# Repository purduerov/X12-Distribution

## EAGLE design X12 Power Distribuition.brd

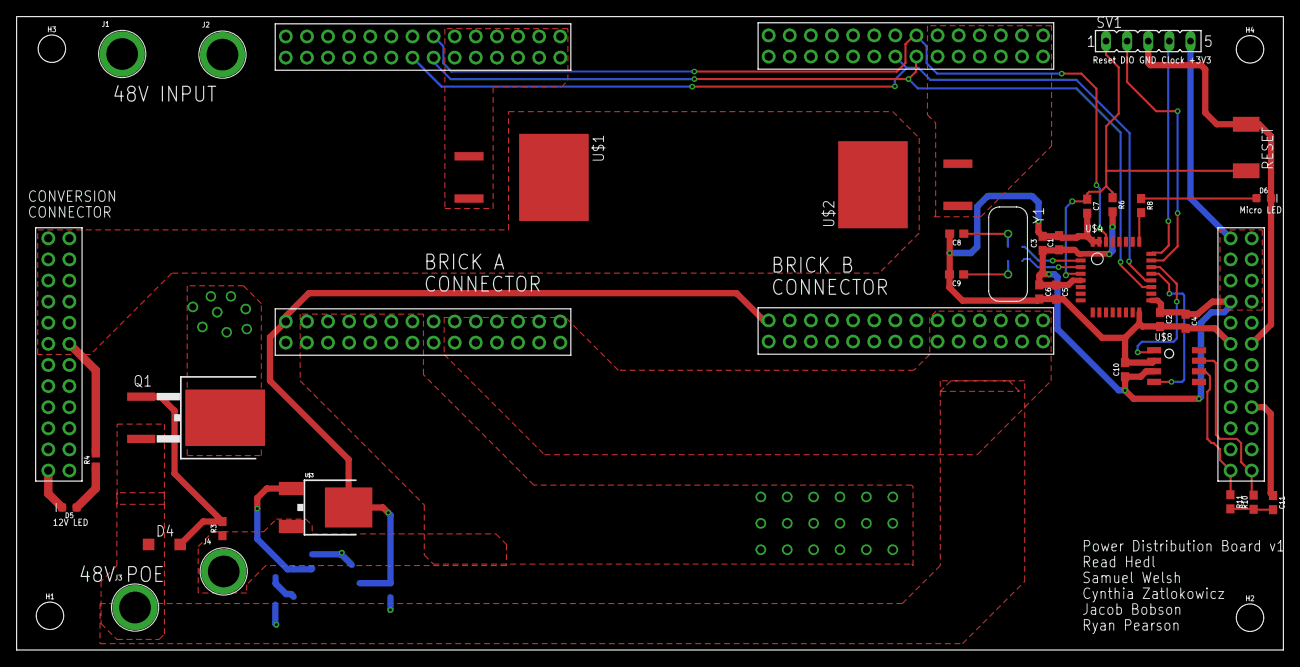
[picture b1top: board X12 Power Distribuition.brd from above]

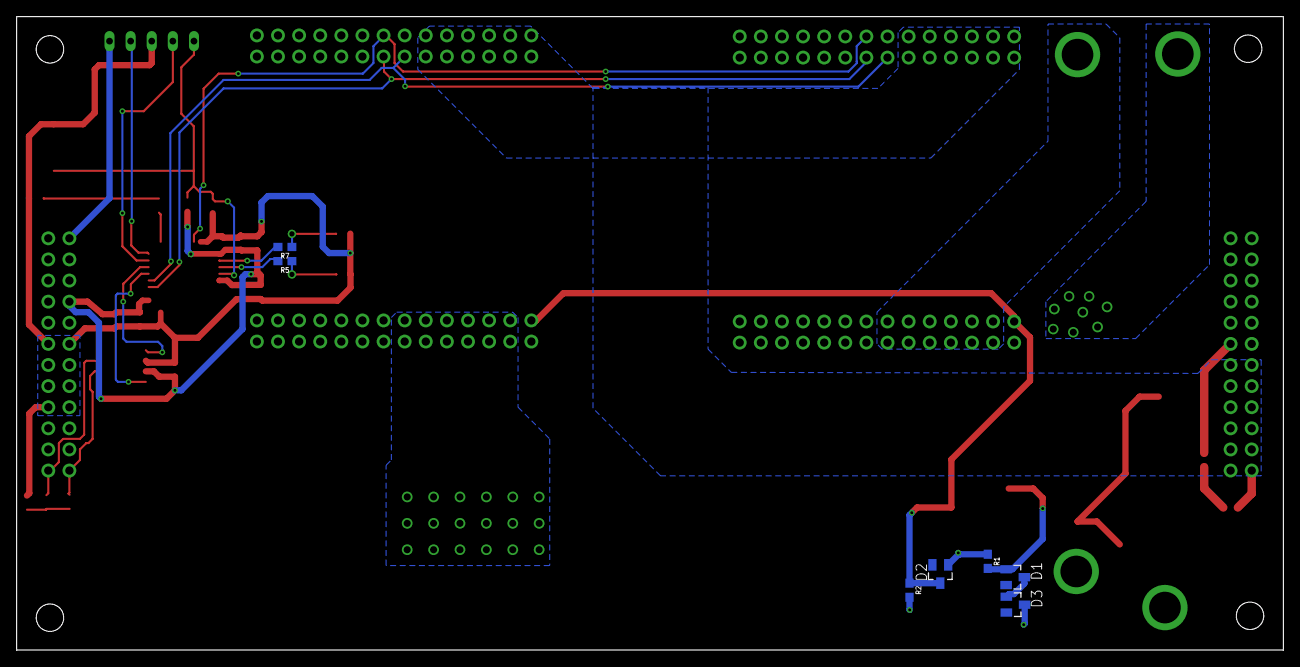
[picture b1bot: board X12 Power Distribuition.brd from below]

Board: 2 copper layers, 152.4 x 76.2 mm, 47 parts (7 on the bottom side), 31 nets.

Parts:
C1, C2, C3, C4, C5, C6, C7, C8, C9, C10: 4.7uF; 0603
C11: 0.1uF; 0603
D1, D3: 22V; SOT23
D2: 5V; SOT23
D4: 15V; SOD123
D5, D6: LED-0603
H1, H2, H3, H4: STAND-OFF
J1, J2, J3, J4: BANANA_CONN
Q1: SPB80P06P; TO263
R1, R3: 1M; 0603
R2: 10K; 0603
R4, R8: 470; 0603
R5, R6, R7: 1k; 0603
R10, R11: 60; 0603
RESET: SW_2512
SV1: FE05-1
U$1, U$2: DIODE
U$3: NMOSFET-DPAK; DPAK
U$4: STM32F042K6T6
U$5, U$7: BRICKBOARD_TSW_14X2
U$6: CONVERSION_TSW_12X2
U$8: TCAN337D
Y1: ECS-80-S-4X; XTAL_ECS-80-S-4X

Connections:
3V3GND: C1.2, C2.2, C3.2, C4.2, C5.2, C6.2, C7.2, C8.2, C9.2, C10.2, C11.1, D6.C, RESET.1, SV1.3, U$4.PB8-BOOT0, U$4.VSS, U$4.VSS1, U$6.35, U$6.36, U$6.37, U$6.38, U$6.39, U$6.40, U$6.41, U$6.42, U$8.GND
48V_GND: D2.1, J2.P$1, J4.P$1, R1.1, R3.1, U$3.3, U$5.3, U$5.4, U$5.5, U$5.6, U$5.7, U$5.8, U$5.9, U$5.10, U$5.11, U$5.12, U$5.13, U$5.14, U$7.3, U$7.4, U$7.5, U$7.6, U$7.7, U$7.8, U$7.9, U$7.10, U$7.11, U$7.12, U$7.13, U$7.14
+3V3: C1.1, C2.1, C3.1, C4.1, C5.1, C6.1, C10.1, R6.2, SV1.5, U$4.VDD, U$4.VDDA, U$4.VDDIO2, U$6.25, U$6.26, U$6.27, U$6.28, U$6.29, U$6.30, U$6.31, U$6.32, U$8.VCC
+12V: R4.2, U$1.OUT, U$2.OUT, U$6.1, U$6.2, U$6.3, U$6.4, U$6.5, U$6.6, U$6.7, U$6.8, U$6.9, U$6.10, U$6.11, U$6.12
+12V_A: U$1.IN1, U$1.IN2, U$7.45, U$7.46, U$7.47, U$7.48, U$7.49, U$7.50, U$7.51, U$7.52, U$7.53, U$7.54, U$7.55, U$7.56
+12V_B: U$2.IN1, U$2.IN2, U$5.45, U$5.46, U$5.47, U$5.48, U$5.49, U$5.50, U$5.51, U$5.52, U$5.53, U$5.54, U$5.55, U$5.56
+48V: D3.3, D4.C, J3.P$1, Q1.2, R2.2, U$5.17, U$5.18, U$5.19, U$5.20, U$5.21, U$5.22, U$5.23, U$5.24, U$5.25, U$5.26, U$5.27, U$5.28, U$7.17, U$7.18, U$7.19, U$7.20, U$7.21, U$7.22, U$7.23, U$7.24, U$7.25, U$7.26, U$7.27, U$7.28
+48V_RAW: J1.P$1, Q1.3
ALERT: U$4.PB7, U$5.43, U$7.43
CAN_H: R10.2, U$6.47, U$8.CANH
CAN_L: R11.1, U$6.48, U$8.CANL
CAN_RX: U$4.PA11, U$8.RXD
CAN_TX: U$4.PA12, U$8.TXD
CLK: U$4.PA9, U$5.44, U$7.44
DATA: U$4.PA10, U$5.42, U$7.42
GND: D5.C, U$5.29, U$5.30, U$5.31, U$5.32, U$5.33, U$5.34, U$5.35, U$5.36, U$5.37, U$5.38, U$5.39, U$5.40, U$6.13, U$6.14, U$6.15, U$6.16, U$6.17, U$6.18, U$6.19, U$6.20, U$6.21, U$6.22, U$6.23, U$6.24, U$7.29, U$7.30, U$7.31, U$7.32, U$7.33, U$7.34, U$7.35, U$7.36, U$7.37, U$7.38, U$7.39, U$7.40
LED: R8.2, U$4.PA15
unnamed: D1.3, D3.1
unnamed: D1.1, R1.2, U$3.1
unnamed: D4.A, Q1.1, R3.2
unnamed: D5.A, R4.1
unnamed: C11.2, R10.1, R11.2
unnamed: C9.1, R5.1, Y1.2
unnamed: C8.1, R7.1, Y1.1
unnamed: D6.A, R8.1
NRST: C7.1, R6.1, RESET.2, SV1.1, U$4.NRST
ON/OFF: D2.3, R2.1, U$3.4, U$5.1, U$7.1
OSC_IN: R7.2, U$4.PF0-OSC_IN
OSC_OUT: R5.2, U$4.PF1-OSC_OUT
SWCLK: SV1.4, U$4.PA14
SWDIO: SV1.2, U$4.PA13

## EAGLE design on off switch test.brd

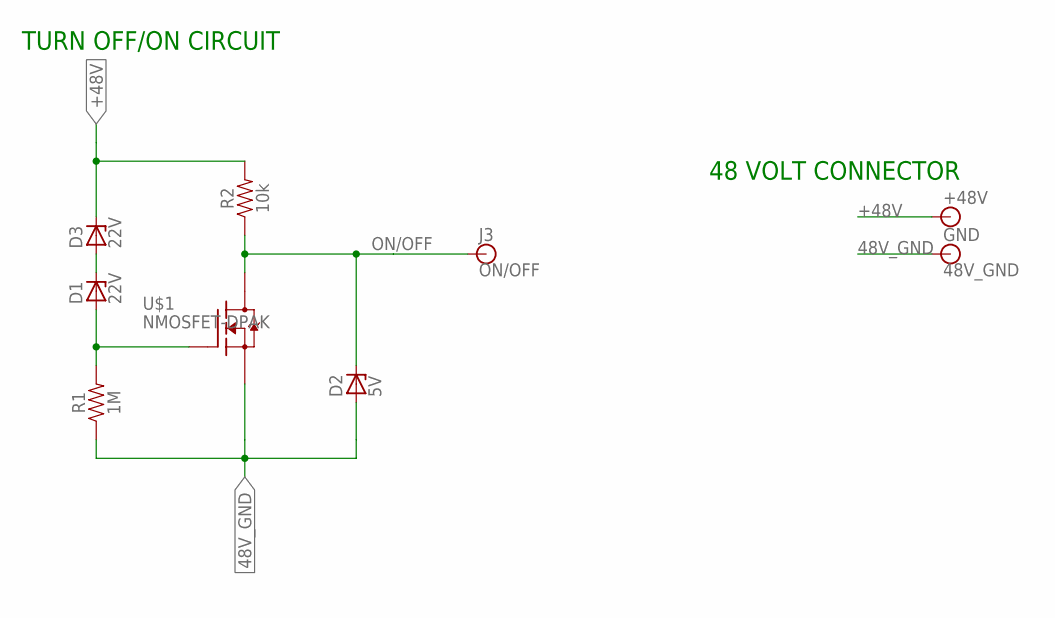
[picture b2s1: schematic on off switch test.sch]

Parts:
+48V: BANANA_CONN
D1, D3: 22V; SOT23
D2: 5V; SOT23
GND: 48V_GND; BANANA_CONN
J3: ON/OFF; BANANA_CONN
R1: 1M; 0603
R2: 10k; 0603
U$1: NMOSFET-DPAK; DPAK

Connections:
48V_GND: D2.1 (A), GND.P$1, R1.1, U$1.3 (S)
+48V: +48V.P$1, D3.3 (C), R2.2
unnamed: D1.3 (C), D3.1 (A)
unnamed: D1.1 (A), R1.2, U$1.1 (G)
ON/OFF: D2.3 (C), J3.P$1, R2.1, U$1.4 (D1)

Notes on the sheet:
48 VOLT CONNECTOR
TURN OFF/ON CIRCUIT

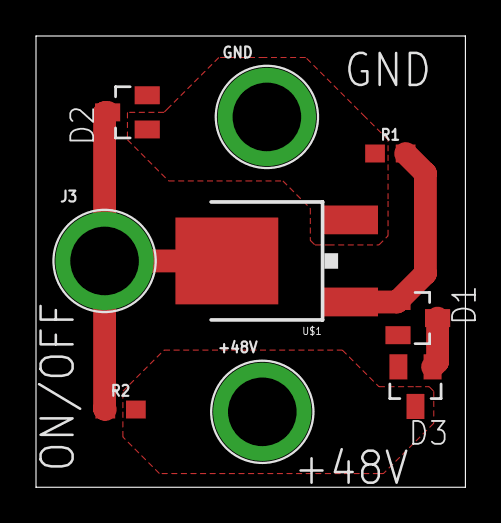
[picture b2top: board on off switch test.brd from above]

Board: 2 copper layers, 23.9 x 25.1 mm, 9 parts (0 on the bottom side), 5 nets.

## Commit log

2019-09-25 created schematic
    (:
2019-09-25 Prelim power distribution schematic
2019-09-25 Test Commit
    Nothing Changed ;)
2019-09-25 Cleaning
2019-10-09 Added Micro
2019-10-12 Micro Added
2019-10-14 Added POE through holes
2019-10-19 Label Fix
2019-10-19 Resistor Values
2019-10-19 clean
2019-10-19 Started Brick Connector
2019-10-22 Prototype Conversion Connector
2019-10-23 test
2019-10-23 Created connectors
2019-10-24 Completed prelim schematic
2019-10-24 created initial connector layout on board
2019-10-29 altered board
2019-10-30 worked on board
2019-11-02 Started Board Placement
2019-11-03 updated connector
2019-11-03 added standoffs
    added the standoffs to the board
2019-11-06 Board
2019-11-06 removed junk pt 1
2019-11-07 modified micro section
2019-11-07 Update X12 Power Distribuition 2.b#1
2019-11-07 Fixed Brickboard Connectors
2019-11-09 finished up prelim board
2019-11-10 fixed some erc warnings
2019-11-10 modified cap placements
2019-11-10 Update X12 Power Distribuition.b##
2019-11-10 more modifications
2019-11-11 Small edits on board
    Added Labels
2019-11-14 Board Fixes around Micro
2019-11-14 Matched Impedances around crystal
2019-11-16 Moved Crystal. Small Fixes
2019-11-16 adjusted thermals
2019-11-16 micro pin label
2019-11-16 minor tweaks
2019-11-21 Final Tweak before Review
2019-11-21 Changed Brick Connectors
    Moved the data signals on brick to middle of connector
2019-11-21 Added traces for new data signals
2019-11-22 V1 finished
2019-11-25 modified thermals
2019-11-25 modified on off ground polygons
2019-11-29 Thermal Fixes around input
2019-12-19 99% Done
2019-12-20 Moved 3V3 Signal and Made CAN TX/RX shorter
2019-12-20 Micro Rerouting
2019-12-20 Final Touches, needs image
2019-12-24 fixed the name placement
2020-01-03 added symbol for copper
2020-01-15 fixed voltage protection circuit
    also removed right angle from a polygon
2020-01-31 Made DXF File

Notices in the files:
parts and their libraries:
SparkFun-Capacitors: Licensing: Creative Commons ShareAlike 4.0 International - https://creativecommons.org/licenses/by-sa/4.0
